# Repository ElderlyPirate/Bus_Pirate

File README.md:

# Bus Pirate

>
> THIS REPOSITORY IS ONLY FOR THE OLD BUS PIRATE v3.x and v4.x HARDWARE!
>
> If you own a Bus Pirate 5 or later, please see https://buspirate.com
>

The Bus Pirate is an open source hacker multi-tool that talks to electronic stuff.
It's got a bunch of features an intrepid hacker might need to prototype their next project.

This community firmware was forked from the official Dangerous Prototypes firmware for these devices.
This repository represents the hard work of community members to sustain and continue the legacy of the Bus Pirate v3 and v4 devices.

## Protocols
    
* 1-Wire
* I2C
* SPI
* JTAG
* Asynchronous serial
* MIDI
* PC keyboard
* HD44780 LCD
* 2- and 3-wire libraries with bitwise pin control
* Scriptable binary bitbang, 1-Wire, I2C, SPI, and UART modes.

## Features

* 0 - 5.5v tolerant pins
* 0 - 6v measurement probe
* 1Hz - 40MHz frequency measurement
* 1kHz - 4MHz pulse-width modulator, frequency generator
* On-board multi-voltage pull-up resistors
* On-board 3.3v and 5v power supplies with software reset
* Macros for common operations
* Bus traffic sniffers (SPI, I2C)
* A bootloader for easy firmware updates
* Transparent USB&rarr;serial mode
* 10Hz - 1MHz low-speed logic analyzer
* Servo driver
* Can program many AVR microcontrollers
  * Supported by AVRdude
  * Can emulate the AVR STK500 v2 (built-in AVRISP-MKII personality)
  * Programs FPGAs and CPLDs with the built-in XSVF JTAG player
* Scriptable from Perl, Python, etc.
* Public domain (Creative Commons Zero) source. Prototype with the Bus Pirate, then use the code in your project however you want. 

## Application Support

The Bus Pirate is used through a simple terminal interface, but these applications also support the Bus Pirate as a programming device, etc.

* [AVRDude] AVR programmer (AVRDude v5.8+, firmware v4 (any) or v5.9+)
* [OpenOCD] JTAG debugger
* [flashrom] bios/flash programmer 

# Purchasing

> 2025 - If you're looking to purchase an old Bus Pirate v3, or v4.. don't
> spend over $30-40 USD. Spend your hard-earned cash on a Bus Pirate 5+ https://buspirate.com

* Bus Pirate v4.0 - *Newer, more space for bigger firmwares*
  * Worldwide: amazon.com has some overpriced old stock boards.

* Bus Pirate v3.6 - *Proven, more well tested*
  * Worldwide: amazon.com has some overpriced old stock boards.
  * Europe: <https://www.robotshop.com/uk/bus-pirate-v36a.html>
  * USA: <https://anibit.com/product/ptt07001>

[OpenOCD]: http://openocd.org
[AVRDude]: http://www.nongnu.org/avrdude
[flashrom]: https://www.flashrom.org/Flashrom

## Firmware Flashing

Refer to [building-and-flashing-firmware](Documentation/building-and-flashing-firmware.md) to see how to build and flash this firmware.

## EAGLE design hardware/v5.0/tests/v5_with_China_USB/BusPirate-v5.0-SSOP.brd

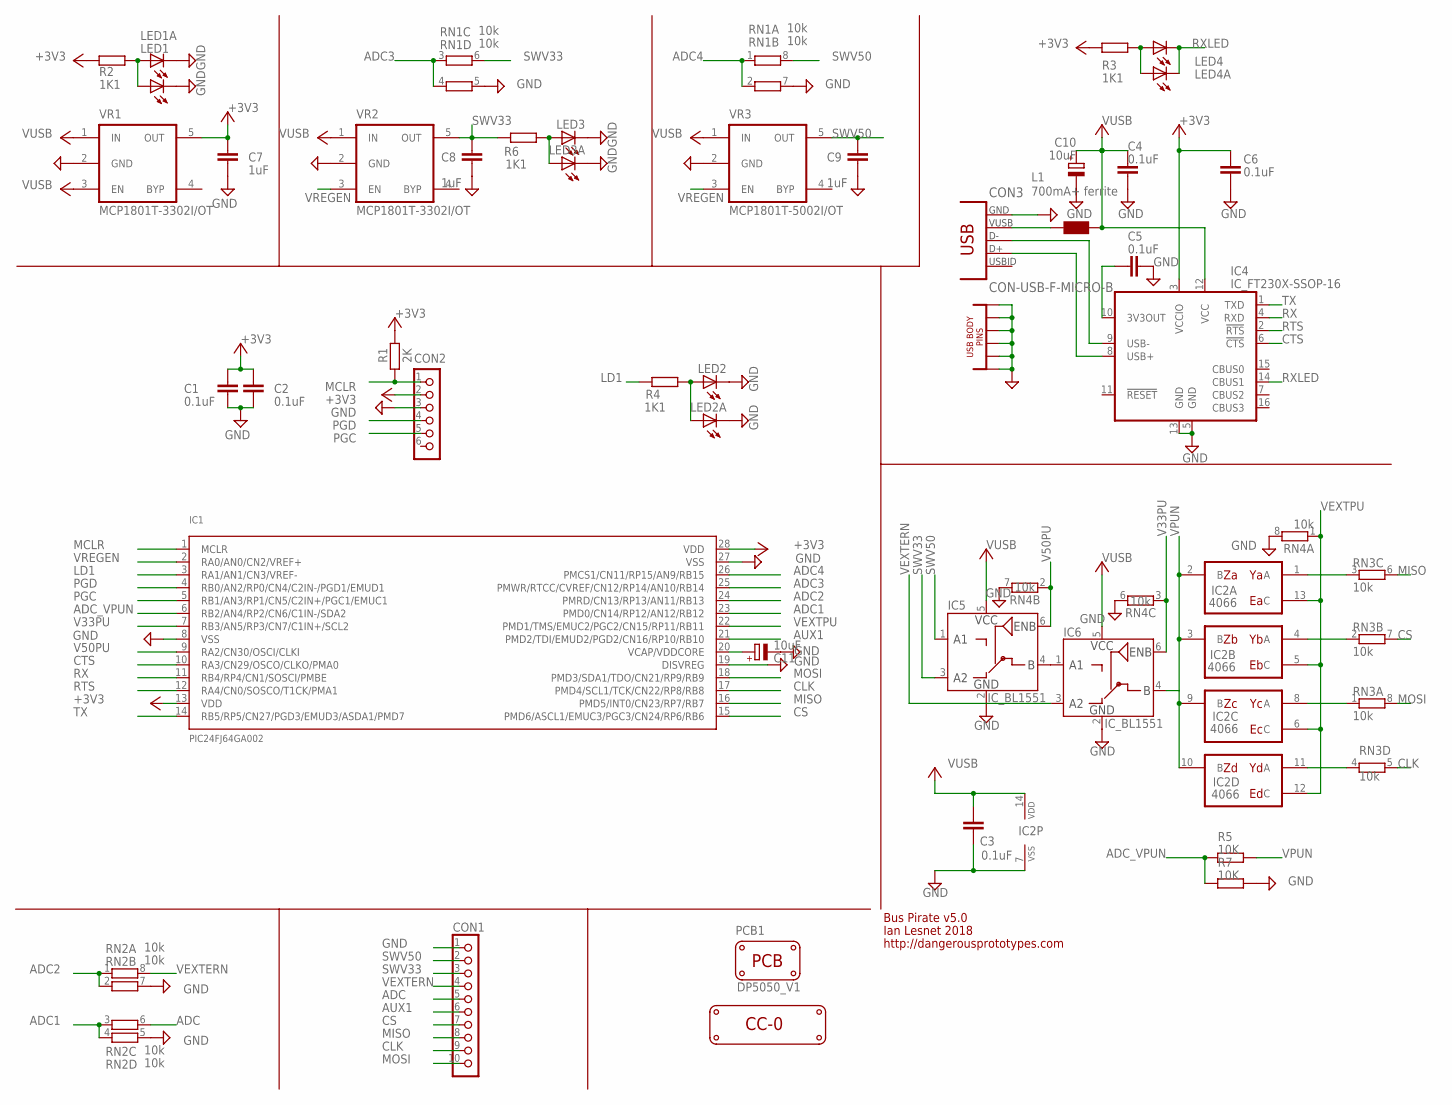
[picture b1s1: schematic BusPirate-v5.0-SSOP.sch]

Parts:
C1, C2, C3, C4, C5, C6: 0.1uF; C603
C7, C8, C9: 1uF; C603
C10, C11: 10uF; SMC_A
CON1: CON_HEADER_1X10-RIGHT_ANGLED_PTH_SHROUDED; M1X10_MALE_RIGHT_ANGLES_PTH_SHROUDED
CON2: CON_HEADER_1X06-PTH; M1X6
CON3: CON-USB-F-MICRO-B; CON_USB_MICRO-B-1-MD05SMXXX-01
IC1: PIC24FJ64GA002; SSOP28
IC2: 4066; TSSOP14
IC4: IC_FT230X-SSOP-16; SSOP-16-FTDI
IC5, IC6: IC_BL1551; SOT-363
L1: 700mA+ ferrite; WE-KI_0805_B
LED1, LED1A, LED2, LED2A, LED3, LED3A, LED4, LED4A: LED-0805; LED-805
LOGO1: LOGO_CC-0
PCB1: PCB_DP_SQUARE-5X5; DP5050_V1
R1: 2K; R603
R2, R3, R4, R6: 1K1; R603
R5, R7: 10K; R603
RN1, RN2, RN3, RN4: 10k; RN8P-4R-CRA06S
VR1, VR2: MCP1801T-3302I/OT; SOT-23-5
VR3: MCP1801T-5002I/OT; SOT-23-5

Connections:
$N26: CON3.P1 (VUSB), L1.2 (1)
+3V3: C1.1, C2.1, C6.1, C7.1, CON2.2, IC1.13 (VDD), IC1.28 (VDD), IC4.3 (VCCIO), R1.2, R2.2, R3.2, VR1.5 (OUT)
ADC: CON1.5, RN2.6 (2)
ADC1: IC1.23 (PMD0/CN14/RP12/AN12/RB12), RN2.3 (1), RN2.4 (1)
ADC2: IC1.24 (PMRD/CN13/RP13/AN11/RB13), RN2.1, RN2.2 (1)
ADC3: IC1.25 (PMWR/RTCC/CVREF/CN12/RP14/AN10/RB14), RN1.3 (1), RN1.4 (1)
ADC4: IC1.26 (PMCS1/CN11/RP15/AN9/RB15), RN1.1, RN1.2 (1)
ADC_VPUN: IC1.6 (RB2/AN4/RP2/CN6/C1IN-/SDA2), R5.2, R7.2
AUX1: CON1.6, IC1.21 (PMD2/TDI/EMUD2/PGD2/CN16/RP10/RB10)
CLK: CON1.9, IC1.17 (PMD4/SCL1/TCK/CN22/RP8/RB8), RN3.5 (2)
CS: CON1.7, IC1.15 (PMD6/ASCL1/EMUC3/PGC3/CN24/RP6/RB6), RN3.7 (2)
CTS: IC1.10 (RA3/CN29/OSCO/CLKO/PMA0), IC4.6 (!CTS)
GND: C1.2, C2.2, C3.2, C4.2, C5.2, C6.2, C7.2, C8.2, C9.2, C10.-, C11.-, CON1.1, CON2.3, CON3.GND1, CON3.GND2, CON3.GND3, CON3.GND4, CON3.GND5, CON3.GND6, CON3.P5 (GND), IC1.8 (VSS), IC1.19 (DISVREG), IC1.27 (VSS), IC2.7 (VSS), IC4.5 (GND), IC4.13 (GND), IC5.2 (GND), IC6.2 (GND), LED1.C, LED1A.C, LED2.C, LED2A.C, LED3.C, LED3A.C, R7.1, RN1.5 (2), RN1.7 (2), RN2.5 (2), RN2.7 (2), RN4.6 (2), RN4.7 (2), RN4.8 (2), VR1.2 (GND), VR2.2 (GND), VR3.2 (GND)
LD1: IC1.3 (RA1/AN1/CN3/VREF-), R4.2
MCLR: CON2.1, IC1.1 (MCLR), R1.1
MISO: CON1.8, IC1.16 (PMD5/INT0/CN23/RP7/RB7), RN3.6 (2)
MOSI: CON1.10, IC1.18 (PMD3/SDA1/TDO/CN21/RP9/RB9), RN3.8 (2)
unnamed: IC2.11 (A), RN3.4 (1)
unnamed: IC2.8 (A), RN3.1
unnamed: C11.+, IC1.20 (VCAP/VDDCORE)
unnamed: IC2.4 (A), RN3.2 (1)
unnamed: IC2.1 (A), RN3.3 (1)
unnamed: LED2.A, LED2A.A, R4.1
unnamed: LED1.A, LED1A.A, R2.1
unnamed: C5.1, IC4.10 (3V3OUT)
unnamed: IC5.4 (B), IC6.1 (A1)
unnamed: LED4.A, LED4A.A, R3.1
unnamed: CON3.P3 (D+), IC4.8 (USB+)
unnamed: CON3.P2 (D-), IC4.9 (USB-)
unnamed: LED3.A, LED3A.A, R6.1
PGC: CON2.5, IC1.5 (RB1/AN3/RP1/CN5/C2IN+/PGC1/EMUC1)
PGD: CON2.4, IC1.4 (RB0/AN2/RP0/CN4/C2IN-/PGD1/EMUD1)
RTS: IC1.12 (RA4/CN0/SOSCO/T1CK/PMA1), IC4.2 (!RTS)
RX: IC1.11 (RB4/RP4/CN1/SOSCI/PMBE), IC4.4 (RXD)
RXLED: IC4.14 (CBUS1), LED4.C, LED4A.C
SWV33: C8.1, CON1.3, IC5.3 (A2), R6.2, RN1.6 (2), VR2.5 (OUT)
SWV50: C9.1, CON1.2, IC5.1 (A1), RN1.8 (2), VR3.5 (OUT)
TX: IC1.14 (RB5/RP5/CN27/PGD3/EMUD3/ASDA1/PMD7), IC4.1 (TXD)
V33PU: IC1.7 (RB3/AN5/RP3/CN7/C1IN+/SCL2), IC6.6 (ENB), RN4.3 (1)
V50PU: IC1.9 (RA2/CN30/OSCI/CLKI), IC5.6 (ENB), RN4.2 (1)
VEXTERN: CON1.4, IC6.3 (A2), RN2.8 (2)
VEXTPU: IC1.22 (PMD1/TMS/EMUC2/PGC2/CN15/RP11/RB11), IC2.5 (C), IC2.6 (C), IC2.12 (C), IC2.13 (C), RN4.1
VPUN: IC2.2 (B), IC2.3 (B), IC2.9 (B), IC2.10 (B), IC6.4 (B), R5.1
VREGEN: IC1.2 (RA0/AN0/CN2/VREF+), VR2.3 (EN), VR3.3 (EN)
VUSB: C3.1, C4.1, C10.+, IC2.14 (VDD), IC4.12 (VCC), IC5.5 (VCC), IC6.5 (VCC), L1.1 (2), VR1.1 (IN), VR1.3 (EN), VR2.1 (IN), VR3.1 (IN)

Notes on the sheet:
Bus Pirate v5.0
Ian Lesnet 2018
http://dangerousprototypes.com

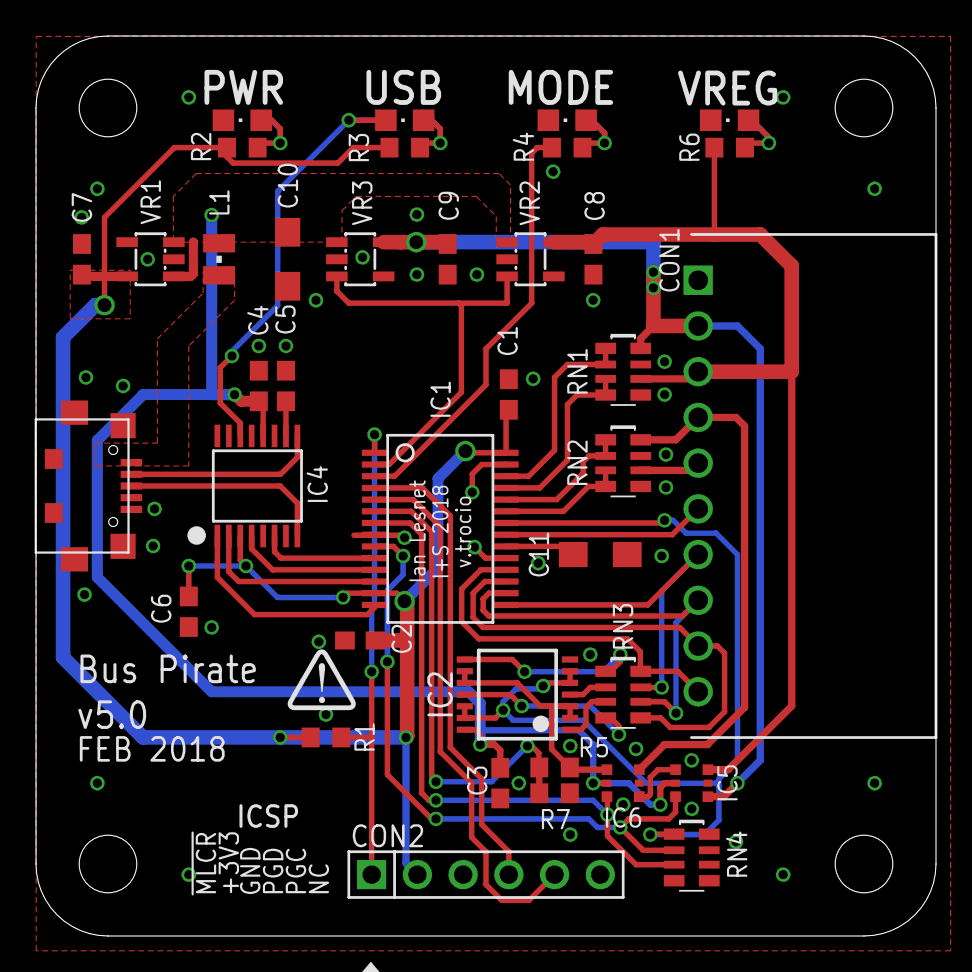
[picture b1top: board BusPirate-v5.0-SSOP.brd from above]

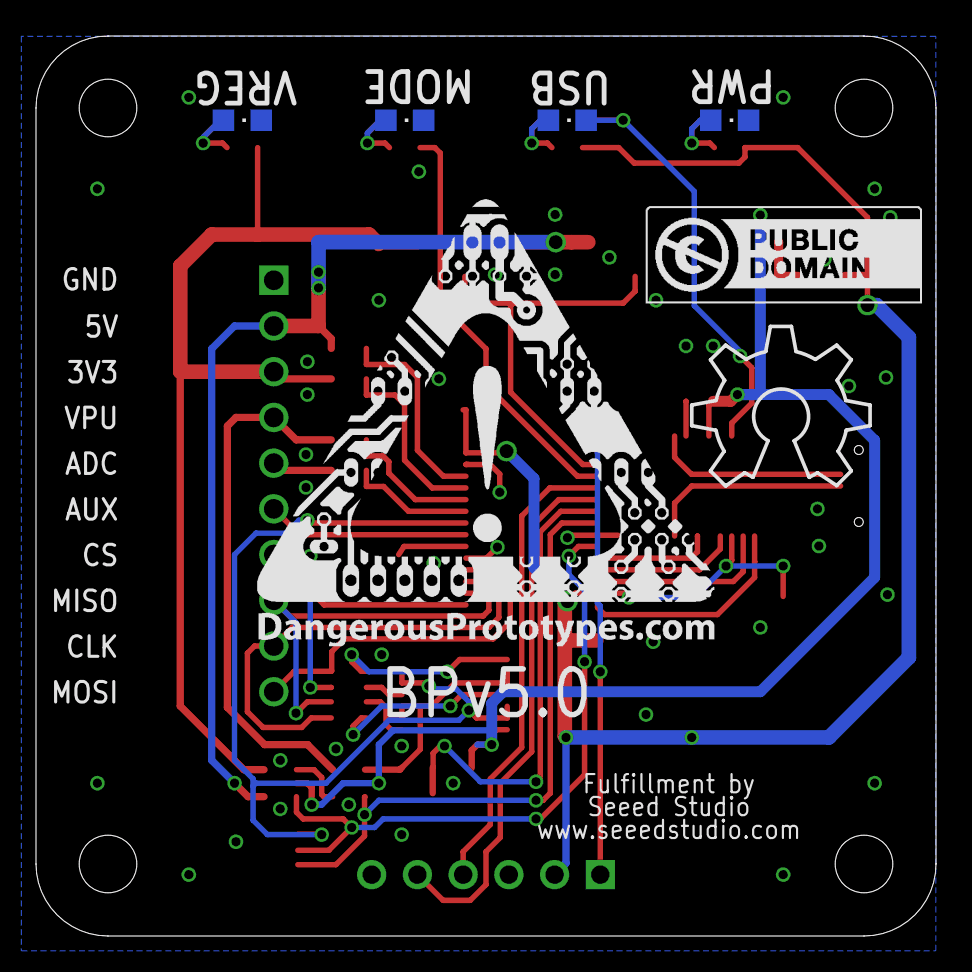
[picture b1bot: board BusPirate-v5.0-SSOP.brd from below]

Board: 2 copper layers, 50.0 x 50.0 mm, 47 parts (7 on the bottom side), 45 nets.

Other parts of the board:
U$1: DP-LOGO
U$2: OSHW_8X350_NOTEXT
U$3: DP_LOGO_ART_1X1

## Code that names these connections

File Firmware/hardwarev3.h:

/*
 * This file is part of the Bus Pirate project
 * (http://code.google.com/p/the-bus-pirate/).
 *
 * Written and maintained by the Bus Pirate project.
 *
 * To the extent possible under law, the project has waived all copyright and
 * related or neighboring rights to Bus Pirate. This work is published from
 * United States.
 *
 * For details see: http://creativecommons.org/publicdomain/zero/1.0/.
 *
 * This program is distributed in the hope that it will be useful, but WITHOUT
 * ANY WARRANTY; without even the implied warranty of MERCHANTABILITY or FITNESS
 * FOR A PARTICULAR PURPOSE.
 */

#ifndef BP_HARDWAREV3_H
#define BP_HARDWAREV3_H

#include "types.h"

/**
 * Set this to 1 if you want to build a v3 firmware that is fully backwards
 * compatible with v2, v2.5, and v2go.
 */
#define BP_VERSION2_SUPPORT 0

#define BP_VERSION_STRING "Bus Pirate v3"
#define BP_VERSION "v3"

#define NUM_OF_SUMP_CHANNELS 5

// this configures the placement of the serial port for
// the PC side terminal interface
// the other modules should be similarly abstracted, but since v0A and v1a share
// pins, it doesn't mater
#define BP_TERM_TX U1TX_IO;
#define BP_TERM_TX_RP RPOR2bits.RP4R
#define BP_TERM_RX RPINR18bits.U1RXR
#define BP_TERM_RX_RP 5

// this is a different type of pin identifier used by the bitbang library
#define AUX 0b0000010000000000  // RB10 on v1, 2, 2go, 3 (not v0)
#define MOSI 0b0000001000000000 // RB9
#define CLK 0b0000000100000000  // RB8
#define MISO 0b0000000010000000 // RB7
#define CS 0b0000000001000000   // RB6
#define IOPOR PORTB
#define IOLAT LATB
#define IODIR TRISB

// these macros set the pin IO used in each module
#define BP_MOSI PORTBbits.RB9
#define BP_CLK PORTBbits.RB8
#define BP_MISO PORTBbits.RB7
#define BP_CS PORTBbits.RB6
#define BP_AUX0 PORTBbits.RB10   // moved pin5 (AUX) to RB10

/*
 * Latch aliases for driving the bus pins.  A write through the PORTx
 * macros is a read-modify-write whose read side returns the pin levels
 * (DS39897C 10.1), so consecutive pin writes re-latch each other with
 * stale levels; outputs are driven through the latches instead.  Reads
 * keep using the PORTx macros above.
 */
#define BP_MOSI_LAT LATBbits.LATB9
#define BP_CLK_LAT LATBbits.LATB8
#define BP_MISO_LAT LATBbits.LATB7
#define BP_CS_LAT LATBbits.LATB6
#define BP_AUX0_LAT LATBbits.LATB10
#define BP_LEDMODE PORTAbits.RA1 // single MODE led on v2a
#define BP_VREGEN PORTAbits.RA0  // single vreg enable pin on v2a
#define BP_PULLUP PORTBbits.RB11 // Pull-up pin on V2a
#define BP_VREGEN_LAT LATAbits.LATA0
#define BP_PULLUP_LAT LATBbits.LATB11
#define BP_LEDMODE_LAT LATAbits.LATA1
#define BP_PGD PORTBbits.RB0     // PGD pin on programming header

// these macros set the direction registers for each IO pin
#define BP_MOSI_DIR TRISBbits.TRISB9
#define BP_CLK_DIR TRISBbits.TRISB8
#define BP_MISO_DIR TRISBbits.TRISB7
#define BP_CS_DIR TRISBbits.TRISB6
#define BP_AUX0_DIR TRISBbits.TRISB10
#define BP_LEDMODE_DIR TRISAbits.TRISA1
#define BP_VREGEN_DIR TRISAbits.TRISA0
#define BP_PULLUP_DIR TRISBbits.TRISB11
#define BP_PGD_DIR TRISBbits.TRISB0

// Open drain/high impedance pin setup
#define BP_MOSI_ODC ODCBbits.ODB9
#define BP_CLK_ODC ODCBbits.ODB8
#define BP_MISO_ODC ODCBbits.ODB7
#define BP_CS_ODC ODCBbits.ODB6
#define BP_AUX0_ODC ODCBbits.ODB10

// Change notice assignment
#define BP_MOSI_CN CNEN2bits.CN21IE
#define BP_CLK_CN CNEN2bits.CN22IE

/*
 * Change notice assignments for the pins bp_aux_pin_read() can select. The
 * device pin table maps RB10 to CN16 and RB6 to CN24, and RB9/RB8 to
 * CN21/CN22 as used above.
 */
#define BP_AUX0_CN CNEN2bits.CN16IE
#define BP_CS_CN CNEN2bits.CN24IE

// ADC assignment
#define BP_ADC_PROBE 12
#define BP_ADC_3V3 10
#define BP_ADC_5V0 9
#define BP_ADC_VPU 11

// ADC pin configuration
#define BP_ADC_PROBE_CFG AD1PCFGbits.PCFG12 // B12/AN12/ADC1/EXT
#define BP_ADC_3V3_CFG AD1PCFGbits.PCFG10   // B14/AN10/ADC3/33V
#define BP_ADC_5V0_CFG AD1PCFGbits.PCFG9    // B15/AN9/ADC4/50V
#define BP_ADC_VPU_CFG AD1PCFGbits.PCFG11   // B13/AN11/ADC2/Vextpullup

#define BL_ADDR_VER 0xABFA

// flow control connections for FTDI chip
// used in uart brige
#define FTDI_RTS_DIR TRISAbits.TRISA4
#define FTDI_RTS PORTAbits.RA4
#define FTDI_CTS_DIR TRISAbits.TRISA3
#define FTDI_CTS PORTAbits.RA3

// defines the PPS input/output for MISO and MOSI pins
#define BP_MISO_RPIN 7
#define BP_MISO_RPOUT RPOR3bits.RP7R
#define BP_MOSI_RPIN 9
#define BP_MOSI_RPOUT RPOR4bits.RP9R

// define the PPS input/output for the AUX pin
#define BP_AUX_RPIN 10
#define BP_AUX_RPOUT RPOR5bits.RP10R
#define BP_CS_RPIN 6
#define BP_CS_RPOUT RPOR5bits.RP6R

// define the PPS input/output for CLK pin
#define BP_CLK_RPIN 8
#define BP_CLK_RPOUT RPOR4bits.RP8R

#define CFG_ADDR_UPPER 0x0000
#define CFG_ADDR_1 0xABFC
#define CFG_ADDR_2 0xABFE

#define PIC_REV_A3 0x3003
#define PIC_REV_B4 0x3042
#define PIC_REV_B5 0x3043
#define PIC_REV_B8 0x3046

static inline void bp_enable_3v3_pullup(void) {}

static inline void bp_disable_3v3_pullup(void) {}

static inline void bp_set_3v3_pullup_state(bool state __attribute__((unused))) {
}

static inline void bp_enable_5v0_pullup(void) {}

static inline void bp_disable_5v0_pullup(void) {}

static inline void bp_set_5v0_pullup_state(bool state __attribute__((unused))) {
}

static inline void bp_enable_usb_led(void) {}

static inline void bp_disable_usb_led(void) {}

static inline void bp_toggle_usb_led(void) {}

static inline void bp_adc_pin_setup(void) {
  BP_ADC_PROBE_CFG = LOW;
  BP_ADC_3V3_CFG = LOW;
  BP_ADC_5V0_CFG = LOW;
  BP_ADC_VPU_CFG = LOW;
}

#endif /* !BP_HARDWAREV3_H */

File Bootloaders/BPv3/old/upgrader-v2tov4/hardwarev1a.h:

/*
 * This file is part of the Bus Pirate project (http://code.google.com/p/the-bus-pirate/).
 *
 * Written and maintained by the Bus Pirate project.
 *
 * To the extent possible under law, the project has
 * waived all copyright and related or neighboring rights to Bus Pirate. This
 * work is published from United States.
 *
 * For details see: http://creativecommons.org/publicdomain/zero/1.0/.
 *
 *    This program is distributed in the hope that it will be useful,
 *    but WITHOUT ANY WARRANTY; without even the implied warranty of
 *    MERCHANTABILITY or FITNESS FOR A PARTICULAR PURPOSE.
 */

//this hardware profile is for the second, surface mount Bus Pirate.
//http://hackaday.com/2009/01/22/how-to-bus-pirate-v1-improved-universal-serial-interface

#define BP_VERSION_STRING "Bus Pirate v1a"
#define BP_VERSION "v1a"

//this configures the placement of the serial port for 
//the PC side terminal interface
//the other modules should be similarly abstracted, but since v0A and v1a share pins, it doesn't mater
//when we move to a USB PIC, we'll need to do that....
#define BP_TERM_TX		U1TX_IO;
#define BP_TERM_TX_RP  	RPOR1bits.RP2R
#define BP_TERM_RX		RPINR18bits.U1RXR
#define BP_TERM_RX_RP	3

//this is a different type of pin identifier used by the bitbang library
#define AUX		0b10000000000 //RB10 on v1, 2, 2go, 3 (not v0)
#define MOSI 	0b1000000000  //RB9
#define CLK 	0b100000000    //RB8
#define MISO 	0b10000000 //RB7
#define CS 		0b1000000 //RB6
#define IOPOR 	PORTB
#define IOLAT	LATB
#define IODIR	TRISB

//these macros set the pin IO used in each module
#define BP_MOSI 		PORTBbits.RB9
#define BP_CLK 			PORTBbits.RB8
#define BP_MISO 		PORTBbits.RB7
#define BP_CS 			PORTBbits.RB6
#define BP_AUX 			PORTBbits.RB10 //moved pin5 (AUX) to RB10
#define BP_PIN6			PORTBbits.RB11
#define BP_LEDMODE		PORTBbits.RB4
#define BP_LEDPWR		PORTAbits.RA3
#define BP_EN50V		PORTAbits.RA4
#define BP_EN33V		PORTBbits.RB5

//these macros set the direction registers for each IO pin
#define BP_MOSI_DIR 	TRISBbits.TRISB9
#define BP_CLK_DIR 		TRISBbits.TRISB8
#define BP_MISO_DIR 	TRISBbits.TRISB7
#define BP_CS_DIR 		TRISBbits.TRISB6
#define BP_AUX_DIR 		TRISBbits.TRISB10
#define BP_PIN6_DIR 	TRISBbits.TRISB11
#define BP_LEDMODE_DIR		TRISBbits.TRISB4
#define BP_LEDPWR_DIR		TRISAbits.TRISA3
#define BP_EN50V_DIR	TRISAbits.TRISA4
#define BP_EN33V_DIR	TRISBbits.TRISB5

//Open drain/high impedance pin setup
#define BP_MOSI_ODC 	ODCBbits.ODB9
#define BP_CLK_ODC 		ODCBbits.ODB8
#define BP_MISO_ODC 	ODCBbits.ODB7
#define BP_CS_ODC 		ODCBbits.ODB6
#define BP_AUX_ODC 		ODCBbits.ODB10

//define the PPS input/output for the AUX pin
#define BP_AUX_RPIN 10	
#define BP_AUX_RPOUT RPOR5bits.RP10R
#define BP_CS_RPIN 6
#define BP_CS_RPOUT RPOR5bits.RP6R

//pseudo function to reset pins to hizstate
//pseudofunctions for voltage regulator switch
#define BP_VREG_ON() BP_EN50V_DIR=0; BP_EN50V=1; BP_EN33V_DIR=0; BP_EN33V=1
#define BP_VREG_OFF() BP_EN50V_DIR=0; BP_EN50V=0; BP_EN33V_DIR=0; BP_EN33V=0

#define BP_AUX2_HI() BP_PIN6_DIR=1;BP_PIN6=0
#define BP_AUX2_LOW() BP_PIN6=0;BP_PIN6_DIR=0
#define BP_AUX2_IN() BP_PIN6_DIR=0;BP_PIN6=0

//define device ID and revision memory location
#define DEV_ADDR_UPPER	0x00FF
#define DEV_ADDR_TYPE	0x0000
#define DEV_ADDR_REV	0x0002
#define CFG_ADDR_UPPER 0x0000
#define CFG_ADDR_1     0xABFC
#define CFG_ADDR_2     0xABFE

// Peripheral Pin Select Outputs
#define NULL_IO		0
#define C1OUT_IO	1
#define C2OUT_IO	2
#define U1TX_IO		3
#define U1RTS_IO	4
#define U2TX_IO		5
#define U2RTS_IO	6
#define SDO1_IO		7
#define SCK1OUT_IO	8
#define SS1OUT_IO	9
#define SDO2_IO		10
#define SCK2OUT_IO	11
#define SS2OUT_IO	12
#define OC1_IO		18
#define OC2_IO		19
#define OC3_IO		20
#define OC4_IO		21
#define OC5_IO		22

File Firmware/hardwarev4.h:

/*
 * This file is part of the Bus Pirate project
 * (http://code.google.com/p/the-bus-pirate/).
 *
 * Written and maintained by the Bus Pirate project.
 *
 * To the extent possible under law, the project has waived all copyright and
 * related or neighboring rights to Bus Pirate. This work is published from
 * United States.
 *
 * For details see: http://creativecommons.org/publicdomain/zero/1.0/.
 *
 * This program is distributed in the hope that it will be useful, but WITHOUT
 * ANY WARRANTY; without even the implied warranty of MERCHANTABILITY or FITNESS
 * FOR A PARTICULAR PURPOSE.
 */

#ifndef BP_HARDWAREV4_H
#define BP_HARDWAREV4_H

#include "types.h"

#define BP_VERSION_STRING "Bus Pirate v4"
#define BP_VERSION "v4"

// If you want to route AUX1 to channel 7 of the JTR SUMP mode in firmware
// then uncomment this line. Otherwise you can "GREEN WIRE" pins 42 to 55
// on the PIC24FJ256GB106 or just have 6 channels that do not include AUX1

#define BPv4_SUMP_SOFT_WIRE
#define NUM_OF_SUMP_CHANNELS 8

// this configures the placement of the serial port for
// the PC side terminal interface
// the other modules should be similarly abstracted, but since v0A and v1a share
// pins, it doesn't mater
#define BP_TERM_TX U1TX_IO;
#define BP_TERM_TX_RP RPOR1bits.RP2R
#define BP_TERM_RX RPINR18bits.U1RXR
#define BP_TERM_RX_RP 11

// this is a different type of pin identifier used by the bitbang library
#define AUX2 0b0000000000000001        // RD0
#define MOSI 0b0000000000000010        // RD1
#define CLK 0b0000000000000100         // RD2
#define MISO 0b0000000000001000        // RD3
#define CS 0b0000000000010000          // RD4
#define AUX0 0b0000000000100000        // RD5
#define SUMP_SPARE6 0b0000000001000000 // RD6
#define SUMP_SPARE7 0b0000000010000000 // RD7
#define AUX1 0b0000000100000000        // RD8

#define IOPOR PORTD
#define IOLAT LATD
#define IODIR TRISD

#define AUX AUX0

// these macros set the pin IO used in each module
#define BP_MOSI PORTDbits.RD1
#define BP_CLK PORTDbits.RD2
#define BP_MISO PORTDbits.RD3
#define BP_CS PORTDbits.RD4
#define BP_AUX0 PORTDbits.RD5    // pin 5 (AUX) is RD5
#define BP_LEDMODE PORTBbits.RB8 // single MODE led on v2a
#define BP_VREGEN PORTBbits.RB9  // single vreg enable pin on v2a
#define BP_PULLUP PORTEbits.RE4  // Pull-up pin on V2a
#define BP_VREGEN_LAT LATBbits.LATB9
#define BP_PULLUP_LAT LATEbits.LATE4
#define BP_LEDMODE_LAT LATBbits.LATB8
#define BP_LEDUSB_LAT LATBbits.LATB10
#define BP_PUVSEL33_LAT LATFbits.LATF4
#define BP_PUVSEL50_LAT LATFbits.LATF5
#define BP_PGD PORTBbits.RB7     // PGD pin on programming header

// new in v4
#define BP_LEDUSB PORTBbits.RB10
#define BP_BUTTON PORTCbits.RC14
#define BP_AUX1 PORTDbits.RD8
#define BP_AUX2 PORTDbits.RD0
#define BP_AUX1_LAT LATDbits.LATD8
#define BP_AUX2_LAT LATDbits.LATD0
#define BP_EE_SDA PORTDbits.RD9
#define BP_EE_SCL PORTDbits.RD10
#define BP_EE_WP PORTDbits.RD11
#define BP_PUVSEL33 PORTFbits.RF4
#define BP_PUVSEL50 PORTFbits.RF5

// these macros set the direction registers for each IO pin
#define BP_MOSI_DIR TRISDbits.TRISD1
#define BP_CLK_DIR TRISDbits.TRISD2
#define BP_MISO_DIR TRISDbits.TRISD3
#define BP_CS_DIR TRISDbits.TRISD4
#define BP_AUX0_DIR TRISDbits.TRISD5
#define BP_LEDMODE_DIR TRISBbits.TRISB8
#define BP_VREGEN_DIR TRISBbits.TRISB9
#define BP_PULLUP_DIR TRISEbits.TRISE4
#define BP_PGD_DIR TRISBbits.TRISB7

// new in v4
#define BP_LEDUSB_DIR TRISBbits.TRISB10
#define BP_BUTTON_DIR TRISCbits.TRISC14
#define BP_AUX1_DIR TRISDbits.TRISD8
#define BP_AUX2_DIR TRISDbits.TRISD0
#define BP_EE_SDA_DIR TRISDbits.TRISD9
#define BP_EE_SCL_DIR TRISDbits.TRISD10
#define BP_EE_WP_DIR TRISDbits.TRISD11
#define BP_PUVSEL33_DIR TRISFbits.TRISF4
#define BP_PUVSEL50_DIR TRISFbits.TRISF5

// secondary MISO/CLK/MOSI connection setup (input, low)
#define BPV4_HWI2CPINS_SETUP()                                                 \
  TRISE |= 0b11100000;                                                         \
  LATE &= (~0b11100000)

// Hardware 'NORMAL' button on BPv4 definitions
#define BP_BUTTON_IF IFS1bits.CNIF
#define BP_BUTTON_SETUP()                                                      \
  BP_BUTTON_DIR = 1;                                                           \
  CNPU1 |= 0b1;                                                                \
  CNEN1 |= 0b1;                                                                \
  IEC1bits.CNIE = 0;                                                           \
  BP_BUTTON_IF = 0;
#define BP_BUTTON_ISDOWN() (!BP_BUTTON) // 0=DOWN (PRESSED) / 1=UP (UNPRESSED)

// Open drain/high impedance pin setup
#define BP_MOSI_ODC ODCDbits.ODD1
#define BP_CLK_ODC ODCDbits.ODD2
#define BP_MISO_ODC ODCDbits.ODD3
#define BP_CS_ODC ODCDbits.ODD4
#define BP_AUX_ODC ODCDbits.ODD5

// Change notice assignment
#define BP_MOSI_CN CNEN4bits.CN50IE
#define BP_CLK_CN CNEN4bits.CN51IE

// ADC assignment
#define BP_ADC_PROBE 1
#define BP_ADC_3V3 0
#define BP_ADC_5V0 2
#define BP_ADC_VPU 5
#define BP_ADC_USB 15

// ADC pin configuration
#define BP_ADC_PROBE_CFG AD1PCFGbits.PCFG2 // AN1/ADC1/EXT
#define BP_ADC_3V3_CFG AD1PCFGbits.PCFG1   // AN0/ADC3/33V
#define BP_ADC_5V0_CFG AD1PCFGbits.PCFG0   // AN2/ADC4/50V
#define BP_ADC_VPU_CFG AD1PCFGbits.PCFG5   // AN5/ADC2/Vextpullup
#define BP_ADC_USB_CFG AD1PCFGbits.PCFG15  // AN15/ADC5/Vusb

// error fixing defines (find with keyword #BPV4
#define OC5CON OC5CON1

//////////// BPv4 Peripheral Pin Select (PPS) Definitions
// Input/Output PPS Definitions
// MISO / MOSI / CS / CLK
#define BP_MISO_RPIN 22
#define BP_MISO_RPOUT RPOR11bits.RP22R
#define BP_MOSI_RPIN 24
#define BP_MOSI_RPOUT RPOR12bits.RP24R
#define BP_CS_RPIN 25
#define BP_CS_RPOUT RPOR12bits.RP25R
#define BP_CLK_RPIN 23
#define BP_CLK_RPOUT RPOR11bits.RP23R
// AUX0:2 (AUX0 = AUX / AUX = AUX0)
#define BP_AUX0_RPIN 20
#define BP_AUX0_RPOUT RPOR10bits.RP20R
#define BP_AUX1_RPIN 2
#define BP_AUX1_RPOUT RPOR1bits.RP2R
#define BP_AUX2_RPIN 11
#define BP_AUX2_RPOUT RPOR5bits.RP11R
// OTHER
#define BP_ADC_RPIN 1
#define BP_ADC_RPOUT RPOR1bits.RP1R

// PPS Compatability
#define BP_AUX_RPIN BP_AUX0_RPIN
#define BP_AUX_RPOUT BP_AUX0_RPOUT

/* DS39897C 26.1, Table 26-1: 256KB part; CFG0/1/2 display CW3/2/1. */
#define CFG_ADDR_UPPER 0x0002
#define CFG_ADDR_0 0xABFA
#define CFG_ADDR_1 0xABFC
#define CFG_ADDR_2 0xABFE

#define PIC_REV_A3 0x0001
#define PIC_REV_A5 0x0003
#define PIC_REV_A6 0x0004

static inline void bp_enable_usb_led(void) {
  BP_LEDUSB_LAT = ON;
  BP_LEDUSB_DIR = OUTPUT;
}

static inline void bp_disable_usb_led(void) {
  BP_LEDUSB_LAT = OFF;
  BP_LEDUSB_DIR = OUTPUT;
}

static inline void bp_toggle_usb_led(void) {
  BP_LEDUSB_LAT ^= ON;
  BP_LEDUSB_DIR = OUTPUT;
}

static inline void bp_adc_pin_setup(void) {
  BP_ADC_PROBE_CFG = LOW;
  BP_ADC_3V3_CFG = LOW;
  BP_ADC_5V0_CFG = LOW;
  BP_ADC_VPU_CFG = LOW;
  BP_ADC_USB_CFG = LOW;
}

static inline void bp_enable_3v3_pullup(void) {
  BP_PUVSEL50_DIR = INPUT;
  BP_PUVSEL33_LAT = LOW;
  BP_PUVSEL33_DIR = OUTPUT;
}

static inline void bp_disable_3v3_pullup(void) {
  BP_PUVSEL50_DIR = INPUT;
  BP_PUVSEL33_LAT = LOW;
  BP_PUVSEL33_DIR = INPUT;
}

static inline void bp_set_3v3_pullup_state(bool state) {
  if (state == ON) {
    bp_enable_3v3_pullup();
  } else {
    bp_disable_3v3_pullup();
  }
}

static inline void bp_enable_5v0_pullup(void) {
  BP_PUVSEL33_DIR = INPUT;
  BP_PUVSEL50_LAT = LOW;
  BP_PUVSEL50_DIR = OUTPUT;
}

static inline void bp_disable_5v0_pullup(void) {
  BP_PUVSEL33_DIR = INPUT;
  BP_PUVSEL50_DIR = INPUT;
}

static inline void bp_set_5v0_pullup_state(bool state) {
  if (state == ON) {
    bp_enable_5v0_pullup();
  } else {
    bp_disable_5v0_pullup();
  }
}

#endif /* !BP_HARDWAREV4_H */

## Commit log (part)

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2023-07-19 XC16 2.10 renamed the C support library file.
2023-09-22 Fix makefile to recompile loader for 64 bit cpus
2023-09-22 Remove old PPC and i386 loader for mac unlikely to be useful in future
2023-09-22 Improve documentation to fix unable to connect error on flash attempt
2024-03-15 flush FTDI buffer to avoid 16ms latency timeout
    with this patch I could cut down the time to read a
    4MB spi flash from 1min to 30sec.
2024-03-31 identify A6 revisions of the PIC24FJ256GB106
2024-03-31 changed bootloader to version 4.12
    1. USB led logic is corrected (was reversed)
    2. pirate-loader hello now works without resetting the buspirate
    3. you get into the bootloader while pressing the mode button at start
    4. changed version to 4.12
2024-03-31 update pirate-loader to 1.0.4
    pirate-loader does not show errors anymore after successful actions
    like hello or flashing new firmware. also better error reporting.
    increased version to 1.0.4
    should be used with bootloader 4.12 but works with 4.10 also
2024-03-31 fix flashrom support for BusPirateV4
    flashrom starts with binary mode and then wants to
    return to interactive mode to get the version and stuff. the method
    to reset only works for BPv3. the BPv4 uses USB which does not like
    the reset. Use another method to get back to the interactive mode.
2024-03-31 changed the spi speed table back to where it was
    A change about 8 years ago made the SPI speed table incompatible
    with the flashrom tool. flashrom thinks it set 8MHz SPI speed when in
    reality it was only 2.6MHz. Changing the table back to the state
    it was to make it (again) compatible with the flashrom tool.
2025-07-10 refactored the spi and usb communication
    massive rewrite of the spi and usb communication for
    faster transfer speeds. this utilizes the spi hardware buffers
    of the pic and interleaves this with the pic usb buffers
